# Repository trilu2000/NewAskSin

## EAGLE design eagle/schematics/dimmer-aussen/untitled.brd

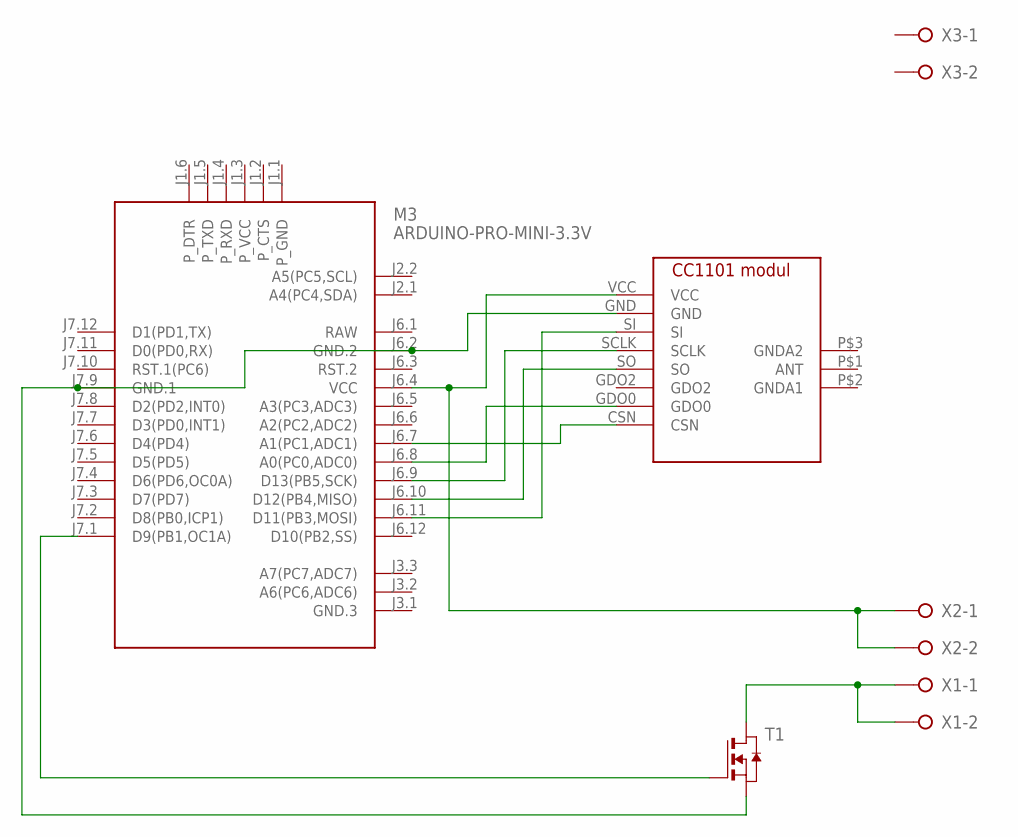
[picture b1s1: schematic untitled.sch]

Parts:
M3: ARDUINO-PRO-MINI-3.3V; ARDUINO-PRO-MINI
T1: NMOSSOT23; SOT-23
U$1: CC1101-MODULEPFOSTEN; PFOSTEN
X1, X2, X3: W237-02P; W237-132

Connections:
unnamed: M3.J6.4 (VCC), U$1.VCC, X2.1, X2.2
unnamed: M3.J6.2 (GND.2), M3.J7.9 (GND.1), T1.2 (S), U$1.GND
unnamed: M3.J6.7 (A1(PC1,ADC1)), U$1.CSN
unnamed: M3.J6.11 (D11(PB3,MOSI)), U$1.SI
unnamed: M3.J6.10 (D12(PB4,MISO)), U$1.SO
unnamed: M3.J6.9 (D13(PB5,SCK)), U$1.SCLK
unnamed: M3.J6.8 (A0(PC0,ADC0)), U$1.GDO0
unnamed: M3.J7.1 (D9(PB1,OC1A)), T1.3 (G)
unnamed: T1.1 (D), X1.1, X1.2
RAW: M3.J6.1 (RAW)

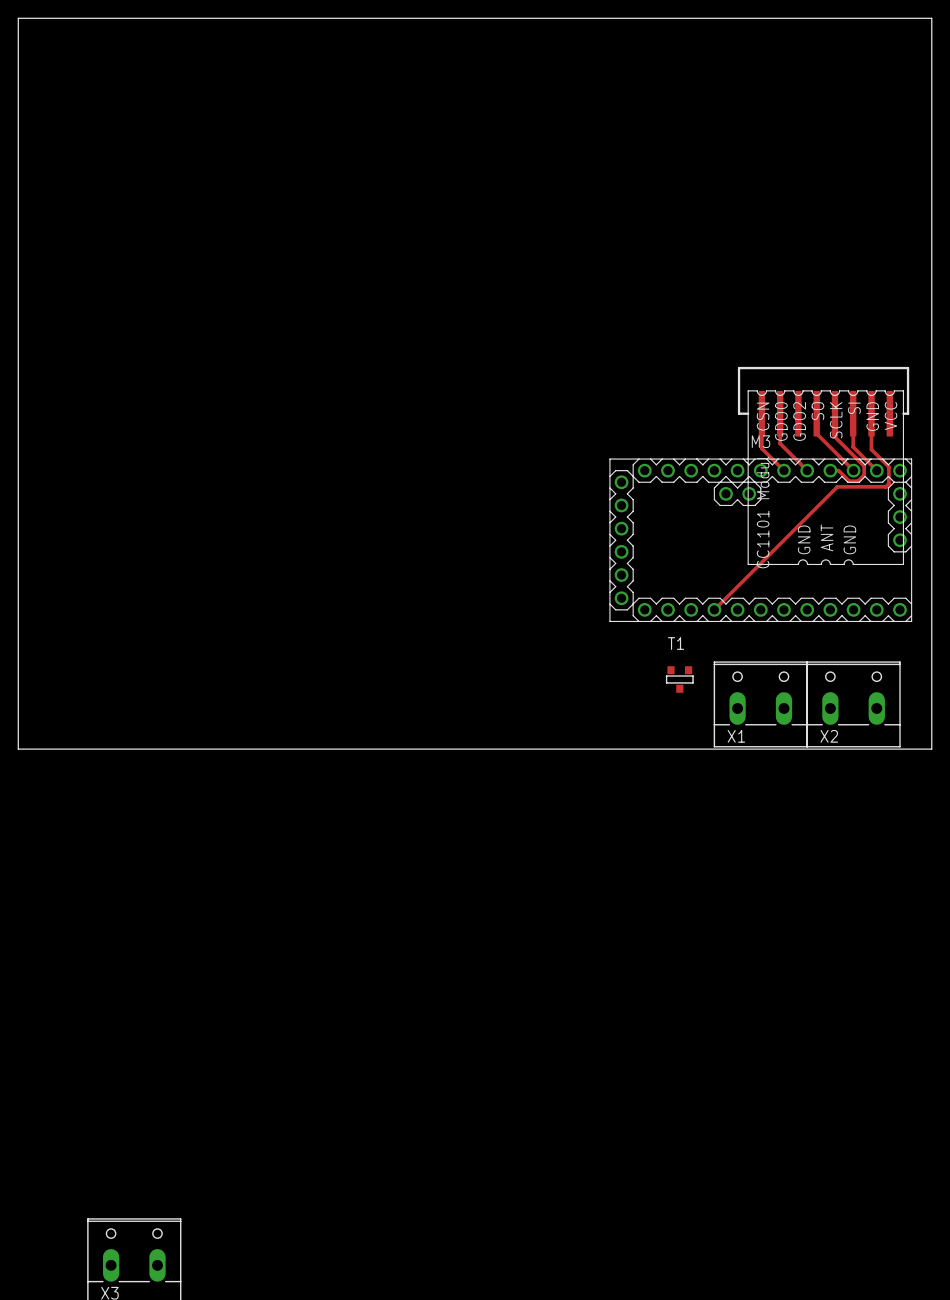
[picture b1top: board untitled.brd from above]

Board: 2 copper layers, 100.0 x 80.0 mm, 6 parts (0 on the bottom side), 9 nets.

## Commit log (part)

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2015-03-08 checked and implemented 32u4 configuration for test sketch
2015-03-08 Custom lux adapted to new structure
2015-03-08 cleanup
2015-03-08 pcb sketch to new structure adopted
2015-03-09 minor
2015-03-10 some work on destillregs
2015-03-13 work on destillregs
2015-03-13 further work on destillregs
2015-04-03 destillregs working
2015-04-09 Add PlatformIO Library Registry manifest file
2015-04-09 Fix compilation error
    - Add include statement for Print.h to HAL.h
2015-06-02 Add method AS::send_generic_event()
2015-06-02 rework of destillregs
2015-06-06 minor change
2015-06-07 Limit allowable payload length to 16 in AS::send_generic_event()
2015-06-07 html README added
2015-06-07 Add doxygen files
2015-06-07 API update
2015-06-07 Add API-documentation for AS and waitTimer
2015-06-07 Add missing code snippet for API docs
2015-06-07 Update API docs
2015-06-08 test
2015-06-09 API docs update
2015-06-10 some test
2015-06-12 Add more structure to doxygen mainpage, add page on protocol basics
2015-06-14 first test of aes signing
2015-06-14 rework random number generation, remove adc dependency
2015-06-14 update spezific hardware setting
2015-06-21 check regarding getstatus
2015-06-27 some improvements
2015-07-04 Add partial API documentation to EEprom.h and EEprom.c
2015-07-04 Update API docs from master
2015-07-07 Add some more documentation for EE
    - Add paragraphs decribing device properties and eeprom memory layout
    - Add references to memory layout to setList and setListArray docs
    - Add description of s_chnTbl, s_peerTbl and s_devDef
2015-10-03 found a error
2015-10-04 start rework of dimmer switch
2015-10-06 changes in destillregs
2015-10-09 some fixes on dimmer
2015-10-10 fixes on dimmer sketch
2015-10-11 rename channel modules
2015-10-11 started with a blind modul
2015-10-11 further work on blind
2015-10-12 further work on blind channel
2015-10-12 work on aes key exchange
2015-10-12 work on aes key exchange, cleanup
2015-10-12 add compiler condition to disable aes support
2015-10-13 rework duplicate code, so we can save about 300 bytes program memory
2015-10-15 keyexchange must be rework
2015-10-15 fix some typos and spaces
2015-10-15 add some doccomments, rework some var names, add checkSendACK(), rework sendEvent and related, add defines for static values
2015-10-15 add some doccomments, rework some var names, add / change defines
2015-10-15 update hex values to upper case
2015-10-15 add some doccomments
2015-10-16 aes_debug
2015-10-16 unify initialisation of random number generator
2015-10-16 some adjustments
2015-10-16 work on storing hmkey in eeprom
2015-10-16 manual merge
2015-10-17 key now saved in eeprom, rework device reset, update excel helper
2015-10-17 add AES for xml helper
2015-10-17 bugfix in helper xls
2015-10-17 some defines
2015-10-17 replace compArray with memcmp
2015-10-18 fix in xls helper
2015-10-18 fix incompletely merge
2015-10-18 manual merge from master
2015-10-19 update comments
2015-10-20 work on AES integration
2015-10-20 optimisations, cleanup
2015-10-20 fix keychange again
2015-10-21 add HM-LC-Bl1-PB-FM_AES excample
2015-10-21 update documantation
2015-10-21 work on AES, refacturing, optimisation, etc
2015-10-21 add register.h for HM-LC-Bl1-PB-FM_AES
2015-10-22 more infos on devicestart for debugging
2015-10-22 update register settings for HM-LC-Bl1-PB-FM - sample
2015-10-22 fix message length
2015-10-22 fix ASE handling if device have more than one channel, fix reset behavior
2015-10-22 fix reset behavior
2015-10-22 some adjustment
2015-10-22 fix aes behavior for devices with more than one channel
2015-10-23 add missing resetStatus
2015-10-23 some work on destiller
2015-10-23 some fixes
2015-10-23 remove bit fields to save som flash memeory
2015-10-25 revert bit field change for mFlg
2015-10-25 work on blind actor
2015-10-25 default handling in destiller
2015-10-26 destiller
2015-10-26 change byte order for REFERENCE_RUNNING_TIME
2015-10-26 change byte order for REFERENCE_RUNNING_TIME back and add macro for change byte order
2015-10-30 some tests
2016-02-19 reworked pcb sketch to work again
2016-02-21 Fix debouncing and simplify code
2016-02-21 fixed LED blinking when pairing
2016-02-26 cc1101 needs no debouncing
2016-03-09 fix wrong structure size
2016-04-14 Updated documentation
2016-04-14 Some optimations, cleanup
2016-04-14 Add posibility to define own ISR functions for PCINT0 - PCINT2 PCINT0-PCINT2 can disabled in HAL_extern.h To disabled PCINT0 - PCINT2 in HAL_extern.h define USE_OWN_ISR_PCINT0_vect USE_OWN_ISR_PCINT1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
2016-04-14 Implement processing of action commands (set, switch remote, ...) in AES mode
2016-04-14 Update defines
2016-04-14 Increase version number
2016-04-16 Fix AES-Handling: PeerID must get from previous buffer
2016-04-16 Remove duplicate code, Cleanup
2016-04-16 Some fixes in Debug-Helper
2016-04-16 Update HM-LC-Bl1-PB-FM_AES Sample
2016-04-18 Add processing of ENTER_BOOTLOADER message
2016-04-18 Manual merge from 2bc1cc0f991bd30036252babb1fb80d4680aa002 Thanks to LineF
2016-04-20 fix debouncing
2016-04-20 size of struct should be one byte
2016-04-20 cleanup code
2016-04-21 startet with a new device
2016-04-21 fix indexing
2016-04-22 further work on new device
2016-04-24 Debug message for RT_INFO
2016-04-24 AS_INFO_RT_STATUS added
2016-04-25 some changes in naming and in destillregs
2016-04-26 ocr should be divider value minus one
2016-04-28 ignore channel when comparing peers
2016-04-29 some work on interrupt function
2016-04-29 different peer messages, length fix
    message 0x70 has other payload than message 0x41
    todo: more differences for other messages?
2016-04-29 fix memory overwrite - perhaps burst bug
2016-05-01 adding new module HM-ES-TX-WM see README.txt for details
2016-05-02 started some work on destillregs2
2016-05-03 add .project to .gitignore
2016-05-08 some changes
2016-05-16 change in pin change interrupt handling
    pcb and dimmer sketch are double checked, HM_PB_6_WM55 are draft and to
    be finished
2016-05-17 further work on the remote sketch
2016-05-17 rework of the Status LED class
    some byte savings and more flixibility. No parameter in register.h
    necassary anymore. LED definition is done in hardware.h...
    Please see example-sketch HM_PB6_WM
2016-05-17 adjusted dimmer and switch to the latest changes in status led class
2016-05-18 some byte saving on status led class while blinkpattern now in progmem
2016-06-13 unnecessary wait removed
2016-06-15 Typos
2016-06-15 much more power saving
2016-07-12 implement have_data answer
2016-07-17 replace all delays (after serial output) with one serial.flush
2016-07-19 fix cc1101 power down
    when powermode is not wakeup_onradio then cc1101 was not correctly sent asleep
2016-07-19 more changes for have_data message processing
2016-07-22 more changes on destillregs
2016-07-29 some further changes on destill regs
2016-07-29 another change
2016-08-01 analyze should work now
2016-08-02 implement default register writing in first time start
2016-08-02 fix index
2016-08-04 change CCA mode and wait for correct state when detecting burst
2016-08-04 set defaults instead of clearing registers on reset_device
2016-08-07 rework of add peers
2016-08-08 some minor change
2016-08-08 setlist while peer add should work
2016-08-12 some further changes in registrar handling
2016-08-12 some further work on registrar
2016-08-15 changes in delegate
    reginas not needed any more
2016-08-18 some further work
2016-08-30 Revert "test on virtual class"
    This reverts commit ead244c76c3b5ceb6cde78f39f7367f0a387d5b9.
2016-08-31 small changes
2016-09-01 Revert "small changes"
    This reverts commit eb88d74bf8bbc7db81794b45d38456cb6f641462.
2016-09-01 Revert "Revert "small changes""
    This reverts commit 808d23be12072d66baf54a06dc53721dc5e5adc0.
2016-09-11 further work on new structure
    new debug flags done via 00_debug-flag.h
    channel master to handle channel communication
    fastdelegate replaced by virtual class
2016-09-14 changes in class handling
2016-09-14 splitted AS in AS and wait_timer class
2016-09-16 start with eeprom dump
2016-09-18 new channel table concept
2016-09-19 clean up and further work on new lchannel module structure
2016-09-20 clean up
2016-09-21 bit more changes i forgot to upload
2016-09-22 some work on new send function
2016-09-30 further changes
    debug reworked, no nasty headers in the respective files any more.
    start to transfer message handling to channel master
    ee_list and ee_peer functions transfered into structs
    send and receive string now in structs for easier handling
2016-10-04 some fixes on send and receive function
2016-10-06 cc1101 reworked, new list handling in channel modules, further changes
2016-10-07 transfered eeprom list functions into struct
2016-10-08 replaced pointer to mbody with union, saved some bytes
2016-10-16 definition of further typedefs, not working yet
2016-10-17 further work on new send and receive functions
2016-10-19 further work on new structure
2016-10-19 new functions in channel master
2016-10-20 fix typo in sendEvent() call
2016-10-20 fix some typos
2016-10-20 add serial.flush()
    all delays (_delay_ms(nn)) due to serial transmits can be deleted
2016-10-21 further work on new messagehandling
2016-10-28 transfer of functions and streamlined the cmSwitch module
2016-10-29 some fixes in cmSwitch
2016-10-30 some bugfixes and implement device reset
2016-10-30 make it nicer
2016-11-01 problems with writing magic
2016-11-01 cleaned up the problem of writing magic byte
2016-11-09 start to rework dimmer sketch
2016-11-11 change in sendstatus
2016-11-16 s60e changes
2016-11-19 some changes in send
2016-11-25 rework of send function
2016-11-28 started with remote sketch
2016-11-29 further work on cmRemote
2016-12-02 cmRemote should work now
2016-12-04 some tests on remote sketch, should work now
2016-12-05 some cleanups and corrections on structure
2016-12-05 some file deletes
2016-12-09 started to implement bidcos
2016-12-09 changes on aes and peer message handling
2016-12-10 further work on AES
2016-12-11 aes key exchange working
2016-12-15 fixed pairing messages
2016-12-16 reworked send function
2016-12-16 some format
2016-12-18 some additions to aes
2016-12-20 rework of config key and reset function (factory defaults)
2016-12-21 start to rework status led class
2016-12-22 rework of led class
2016-12-23 further work to avoid hardware.h file in user sketch folder
    interrupt and pin handling reworked
2016-12-26 some further work on HAL and debug stuff
2016-12-26 further work on bat measurement
2017-01-09 further work on battery sensor
2017-01-11 further work on hw abstraction layer
2017-01-12 some work on the file structure and dependencies
2017-01-13 reworked classes and changed to a more pointer approach to save memory
2017-01-16 some update
2017-01-17 fix battery measurement
    # Conflicts:
    # HAL_atmega.cpp
    # Conflicts:
    # HAL_atmega.cpp
    # Conflicts:
    # HAL_atmega.cpp
2017-01-18 some structural changes
2017-01-20 worked on test sketches
2017-01-23 graphical overview of library
2017-01-27 some further work on dimmer
2017-01-28 fix some compiler errors
2017-01-28 changes in eeprom handling and dimmer tests
2017-01-28 further work on dimmer
2017-01-28 default arguments back to .h file
2017-01-29 fix some compiler errors again
2017-01-29 add Serial.flush() before setSleep
2017-01-29 all channels gets informed of a list change
2017-02-03 inform on config change in all channel
2017-02-05 further work on state machine in dimmer
2017-02-09 further work on dimmer channel
2017-02-10 build virtual channel handling in dimmer
2017-02-10 updated docu on findings for the dimmer
2017-02-12 fix msg counter when peered
2017-02-15 broadcast flag in sendfunction
2017-02-17 further work on dimmer messaging
2017-02-17 test on pwm frequency
2017-02-19 message analyse für status message dimmer
2017-02-20 some changes on status messages
2017-02-20 fix memory leak
2017-02-21 more new() replacements
2017-02-26 some smaller fixes
2017-02-26 default writing on peer optimized
2017-02-26 default write changed again
2017-03-08 some cleanup
2017-03-09 some rework of virtual classes definition
2017-03-16 config status request and some minor changes
2017-03-17 remote works again
2017-03-19 some rework on dimmer
2017-03-31 some rework on dimmer again
    list1 now working
    optimization of pwm
2017-04-01 some work on pwm
2017-04-02 new eagle folder
2017-04-13 some changes in led and config button class
2017-04-13 some smaller changes

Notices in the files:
parts and their libraries:
diy-modules: Released under the Creative Commons Attribution 4.0 International License: http://creativecommons.org/licenses/by/4.0
